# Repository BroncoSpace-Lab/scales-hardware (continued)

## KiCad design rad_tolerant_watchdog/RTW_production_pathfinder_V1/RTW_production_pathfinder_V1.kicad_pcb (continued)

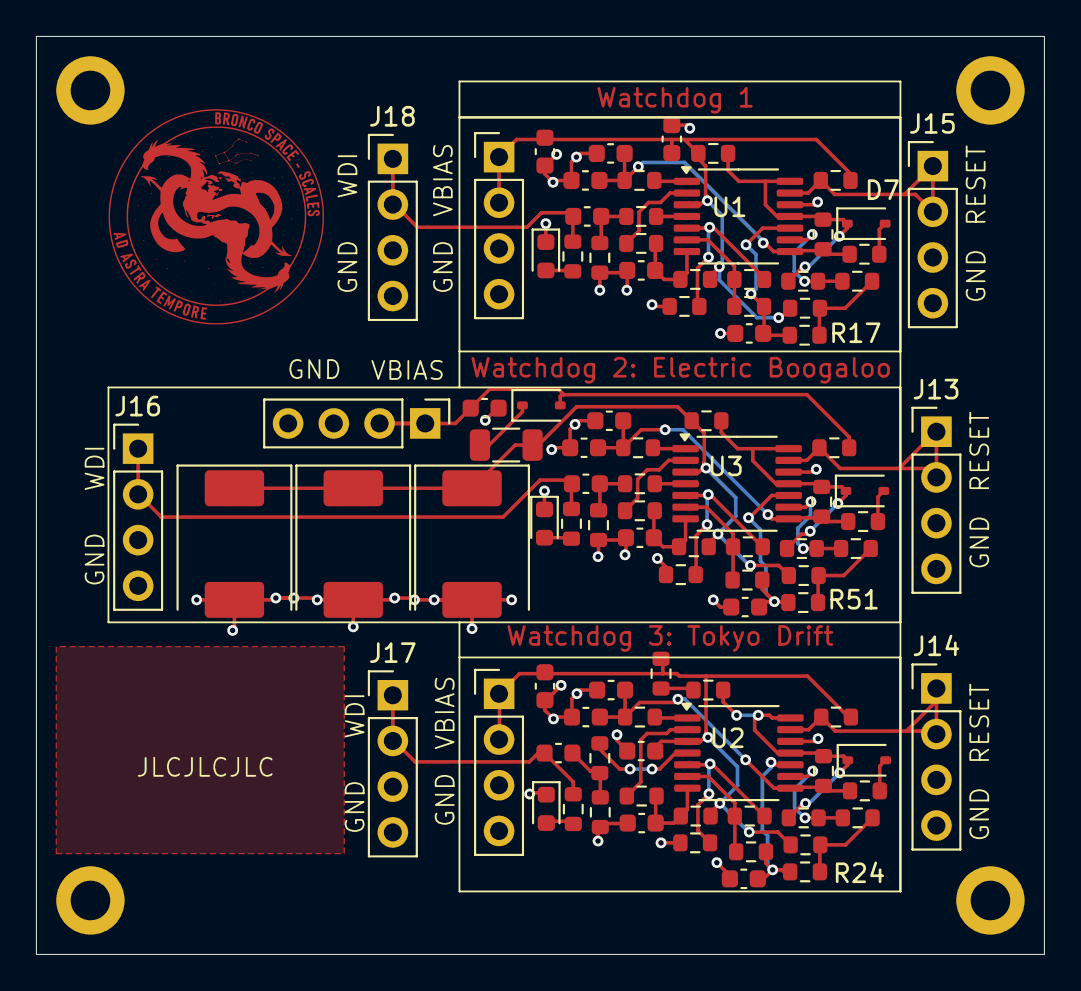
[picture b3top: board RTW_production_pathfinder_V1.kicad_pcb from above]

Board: 2 copper layers, 56.0 x 51.0 mm, 99 parts (0 on the bottom side), 55 nets.

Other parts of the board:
C38: 10u; C_0603_1608Metric

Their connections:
GND: C38.2; also elsewhere on the board
VBIAS_1: C38.1; also elsewhere on the board
